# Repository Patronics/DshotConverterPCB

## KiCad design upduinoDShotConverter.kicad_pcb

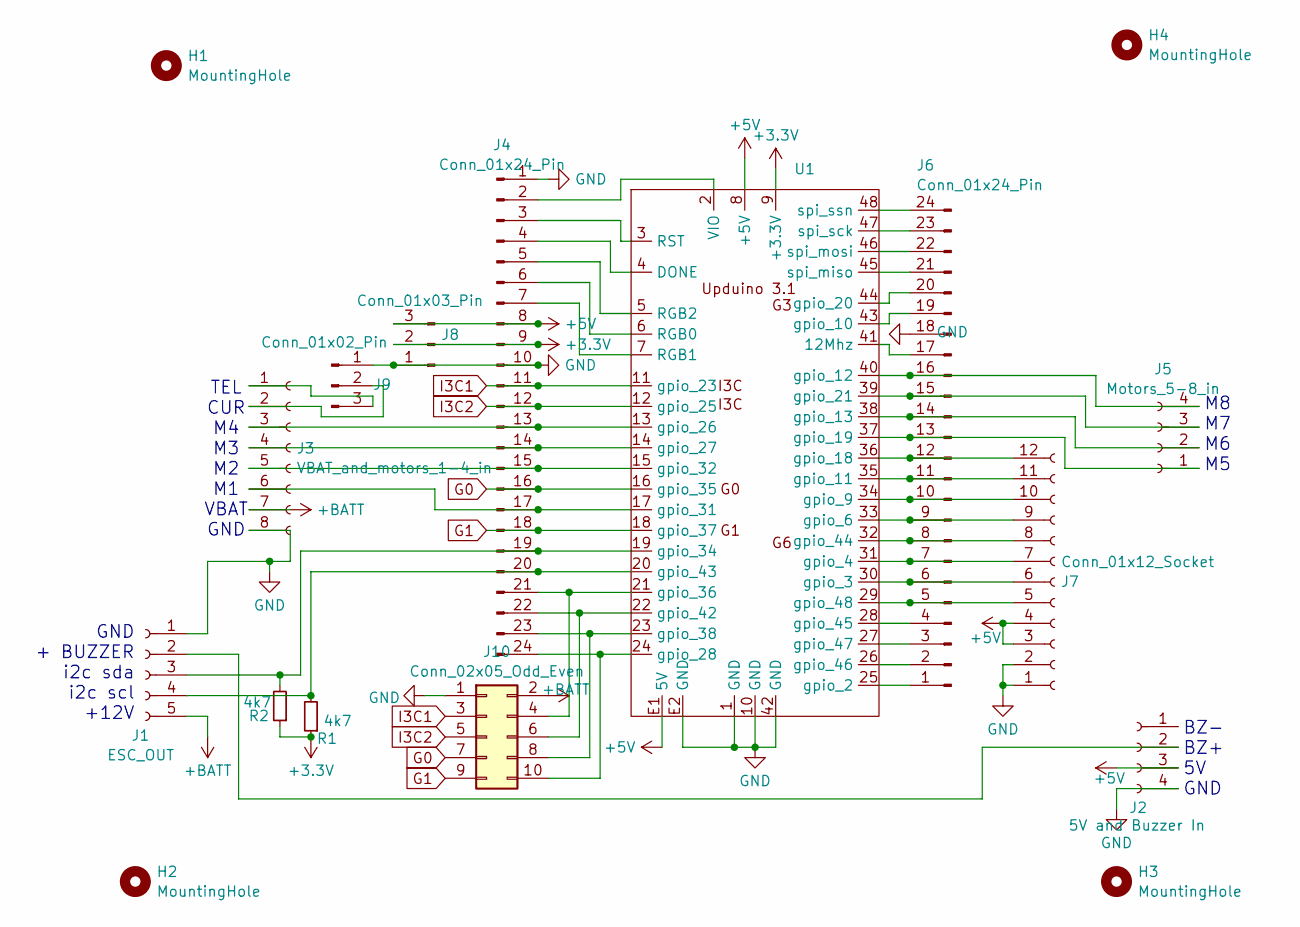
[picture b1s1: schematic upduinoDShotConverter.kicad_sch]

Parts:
H1, H2, H3, H4: MountingHole; MountingHole_3.2mm_M3_Pad
J1: ESC_OUT; Molex_PicoBlade_53261-0571_1x05-1MP_P1.25mm_Horizontal; LCSC C392176
J2: 5V and Buzzer In; JST_SH_SM04B-SRSS-TB_1x04-1MP_P1.00mm_Horizontal; LCSC C160404
J3: VBAT_and_motors_1-4_in; JST_SH_SM08B-SRSS-TB_1x08-1MP_P1.00mm_Horizontal; LCSC C160407
J4, J6: Conn_01x24_Pin; PinHeader_1x24_P2.54mm_Vertical
J5: Motors_5-8_in; JST_SH_SM04B-SRSS-TB_1x04-1MP_P1.00mm_Horizontal; LCSC C160404
J7: Conn_01x12_Socket; JST_SH_SM12B-SRSS-TB_1x12-1MP_P1.00mm_Horizontal; LCSC C160411
J8: Conn_01x03_Pin; PinHeader_1x03_P2.54mm_Vertical
J9: Conn_01x02_Pin; PinHeader_1x03_P2.54mm_Vertical
J10: Conn_02x05_Odd_Even; PinHeader_2x05_P2.54mm_Vertical
R1, R2: 4k7; R_0603_1608Metric; LCSC C23162
U1: Upduino 3.1

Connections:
+3.3V: J4.9, J8.2, R1.1, R2.1, U1.9 (+3.3V)
+5V: J2.3, J4.8, J7.3, J7.4, J8.3, U1.8 (+5V), U1.E1 (5V)
+BATT: J1.5, J3.7, J10.2
G0: J4.16, J10.7, U1.16 (gpio_35)
G1: J4.18, J10.9, U1.18 (gpio_37)
GND: J1.1, J2.4, J3.8, J4.1, J4.10, J6.18, J7.1, J7.2, J8.1, J9.1, J10.1, U1.1 (GND), U1.10 (GND), U1.42 (GND), U1.E2 (GND)
I3C1: J4.11, J10.3, U1.11 (gpio_23)
I3C2: J4.12, J10.5, U1.12 (gpio_25)
unnamed: J1.2, J2.2
unnamed: J1.3, J4.19, R2.2, U1.19 (gpio_34)
unnamed: J1.4, J4.20, R1.2, U1.20 (gpio_43)
unnamed: J3.1, J9.3
unnamed: J3.2, J9.2
unnamed: J3.3, J4.13, U1.13 (gpio_26)
unnamed: J3.4, J4.14, U1.14 (gpio_27)
unnamed: J3.5, J4.15, U1.15 (gpio_32)
unnamed: J3.6, J4.17, U1.17 (gpio_31)
unnamed: J4.2, U1.2 (VIO)
unnamed: J4.3, U1.3 (RST)
unnamed: J4.4, U1.4 (DONE)
unnamed: J4.5, U1.5 (RGB2)
unnamed: J4.6, U1.6 (RGB0)
unnamed: J4.7, U1.7 (RGB1)
unnamed: J5.1, J6.13, U1.37 (gpio_19)
unnamed: J5.2, J6.14, U1.38 (gpio_13)
unnamed: J5.3, J6.15, U1.39 (gpio_21)
unnamed: J5.4, J6.16, U1.40 (gpio_12)
unnamed: J6.1, U1.25 (gpio_2)
unnamed: J6.2, U1.26 (gpio_46)
unnamed: J6.3, U1.27 (gpio_47)
unnamed: J6.4, U1.28 (gpio_45)
unnamed: J6.5, J7.5, U1.29 (gpio_48)
unnamed: J6.6, J7.6, U1.30 (gpio_3)
unnamed: J6.7, J7.7, U1.31 (gpio_4)
unnamed: J6.8, J7.8, U1.32 (gpio_44)
unnamed: J6.9, J7.9, U1.33 (gpio_6)
unnamed: J6.10, J7.10, U1.34 (gpio_9)
unnamed: J6.11, J7.11, U1.35 (gpio_11)
unnamed: J6.12, J7.12, U1.36 (gpio_18)
unnamed: J6.17, U1.41 (12Mhz)
unnamed: J6.19, U1.43 (gpio_10)
unnamed: J6.20, U1.44 (gpio_20)
unnamed: J6.21, U1.45 (spi_miso)
unnamed: J6.22, U1.46 (spi_mosi)
unnamed: J6.23, U1.47 (spi_sck)
unnamed: J6.24, U1.48 (spi_ssn)
unnamed: J4.21, J10.4, U1.21 (gpio_36)
unnamed: J4.22, J10.6, U1.22 (gpio_42)
unnamed: J4.23, J10.8, U1.23 (gpio_38)
unnamed: J4.24, J10.10, U1.24 (gpio_28)

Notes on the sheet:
GND + BUZZER i2c sda i2c scl +12V
M8 M7 M6 M5
TEL CUR M4 M3 M2 M1 VBAT GND
BZ- BZ+ 5V GND

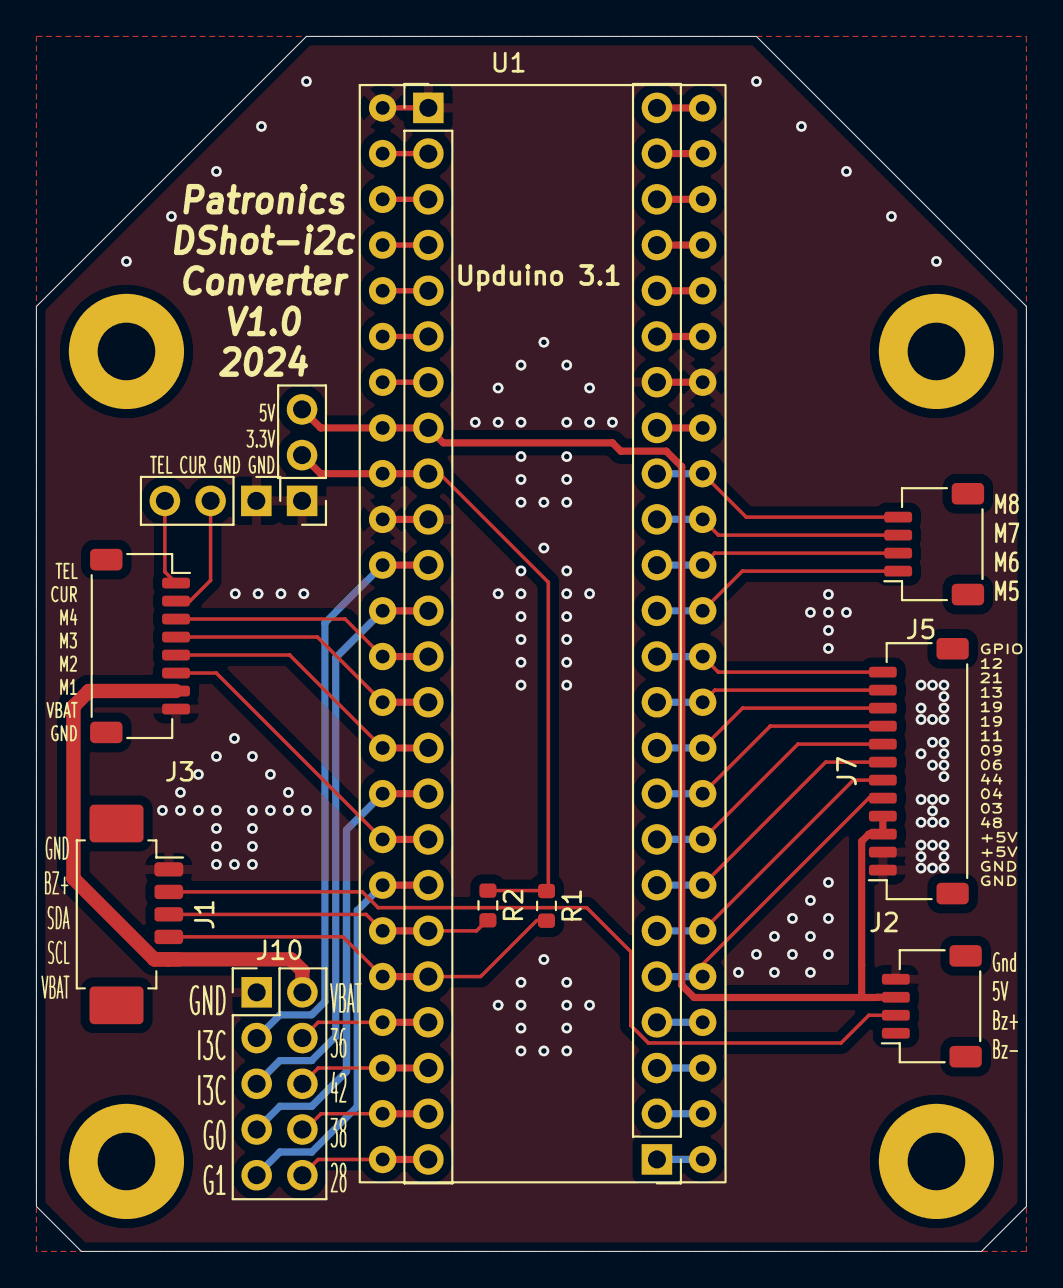
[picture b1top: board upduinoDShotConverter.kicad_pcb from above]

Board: 2 copper layers, 55.0 x 67.5 mm, 17 parts (0 on the bottom side), 50 nets.

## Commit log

2024-08-29 intitial commit, most of key layout complete
2024-08-29 chamfer corners
2024-08-29 lots of tweaks, solid design. About to attempt orientation shift
2024-08-29 sucessful orientation shift, along with additional GPIO breakouts and via arrows
2024-08-29 finalize design for v1.0 release, and assign parts from LCSC/JLCPCB
